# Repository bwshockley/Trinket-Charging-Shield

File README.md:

# Trinket-Battery-Shield
Adafruit Trinket Shield for Battery Charging and RGB status LED.

Version B

## About
This is an add-on circuit board for the [Adafruit Trinkets](https://www.adafruit.com/?q=trinket&).  This board adds a battery connector with an MCP73831 Lithium-Ion/Lithium-Polymer battery charger set at 100mAH charging.
The charger has two indicator LEDs, one to indicate the battery is currently charging from the micro-usb port on the Trinket, and the other to indicate when the battery has fully charged.

Version B of the board has the connections reversed such that this board and the Trinket can back connected "back-to-back" so that the reset button and from LEDs (On and #1) can be accessed.  BOM is identical.

## Boards
PCBs can be ordered direct [through OSHPARK.com](https://oshpark.com/shared_projects/fXX7IH66).

[Version B here.](https://oshpark.com/shared_projects/0WDgFbOp)

## WS2812B LED
There is a pad for a WS2812B RGB LED.  This LED is connected to data pin #0.  The user can leave this LED unpopulated if only battery charging capability is required.

## Battery Power
Note that the Adafruit Trinkets come with circuits for using the battery power and automatically switching between USB power and battery power as needed.  If the user only wishes to have battery power and not the charging capability, the user only needs to populate the JST 2-Pin connector on the back of the Trinket.

## BOM
C1, C2 = 0805 series SMT capcitors 10uF and at least 10V to be safe.
R1, R2 = 0805 resistors.  These resistors determine the current each status LED uses.  Charging LED should not sink more than 25mA, and Done LED should not source more than 35mA.
R3 = 0805 resistor at 10KOhm.  This sets the charger at 100mAh.  Other values possible.  Recommend 100mAh.

IC1 = MCP73831T battery charging IC.

J1 = JST-2_SMD - Available via Adafruit, Sparkfun, or Mouser.

LEDs = 0805 LEDs. Not necessary for circuit to work.  Recommended LEDS:

* SML-LX0805SOC-TR (Orange) Charging LED with R1 = 390Ohm minimum
* SML-LX0805SUGC-TR (Green) Charged or Done LED with R2 = 270Ohm minimum

WS2812B LED - Not necessary, but if the user chooses to add, LED must be 5050 size.

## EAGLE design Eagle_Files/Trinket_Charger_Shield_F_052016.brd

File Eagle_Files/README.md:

#Eagle Files
All files were designed with CadSoft Eagle PCB Design v7.5 (Eagle).  These files are provided AS IS and are not to be used for commercial purpose.
CadSoft provides several licensing options for Eagle, including a [Freeware license](http://www.cadsoftusa.com/download-eagle/freeware/) and a
[commercial light](http://www.cadsoftusa.com/eagle-pricing/) license.  Additional information
can be found on the [CadSoft website](http://www.cadsoftusa.com)

#BRD and SCH
The BRD (Board) files are the physical board layout files and the SCH (Schematic) files are the schematic for the circuit.

#GERBERS
I will upload the latest GERBER files as soon as possible.  GERBER files are industry standard and can be sent to almost any PCB manufacturer.
They do not require the use of CadSoft Eagle to view and use.

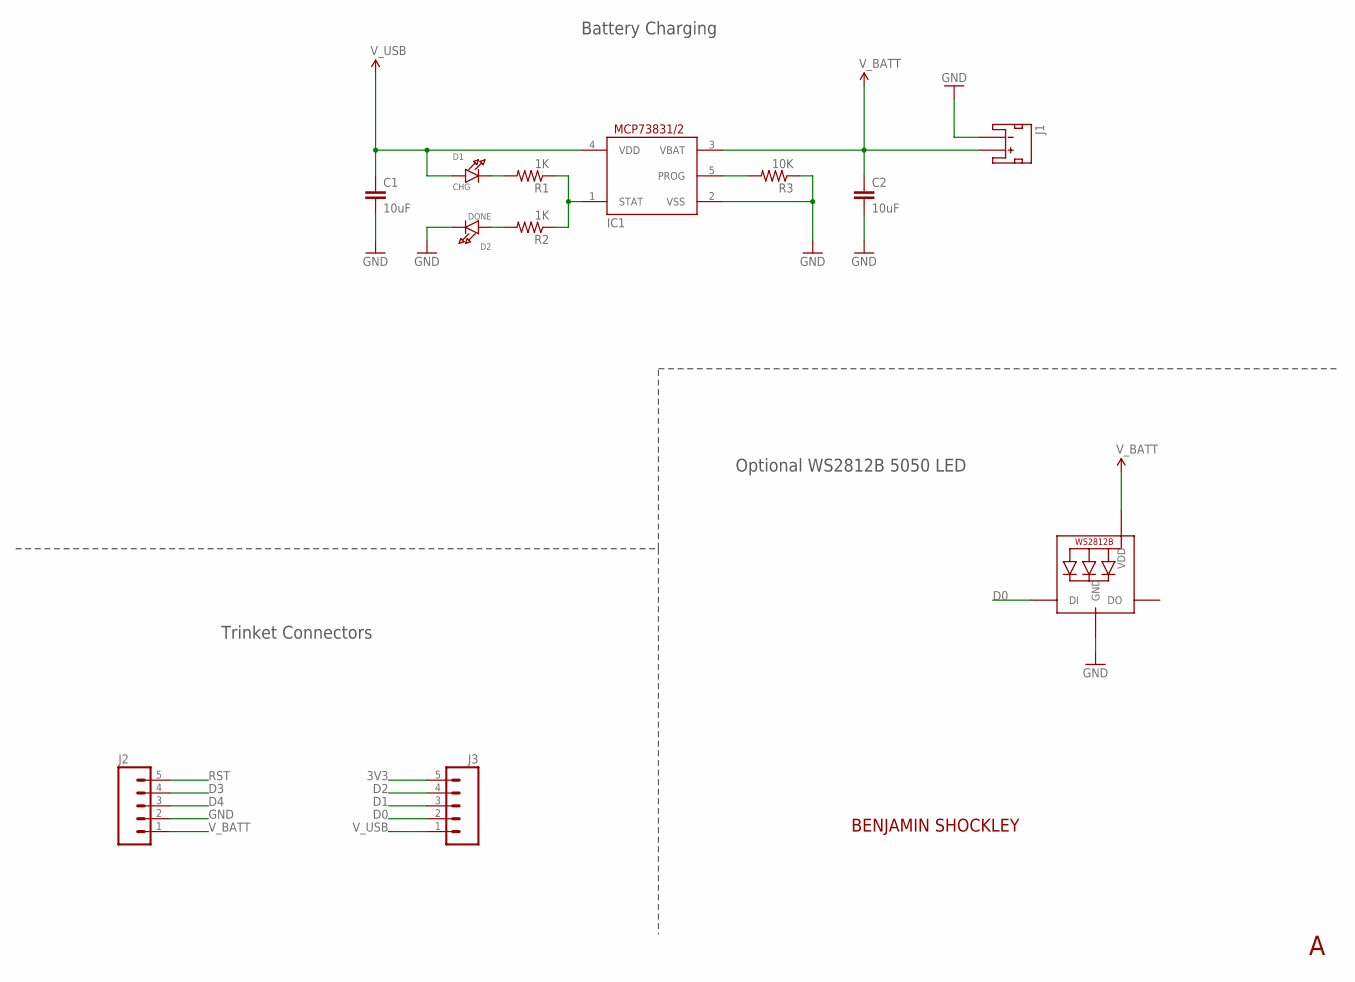
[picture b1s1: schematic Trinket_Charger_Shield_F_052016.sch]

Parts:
C1, C2: 10uF; 0805
D1: CHG; CHIPLED_0805_NOOUTLINE
D2: DONE; CHIPLED_0805_NOOUTLINE
IC1: MCP73831/OT; SOT23-5L
J1: JST_2MM_MALE; JST-2-SMD
J2, J3: M05NO_SILK; 1X05_NO_SILK
LED: WS2812B5050; WS2812B
R1, R2: 1K; 0805
R3: 10K; 0805

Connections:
3V3: J3.5
D0: J3.2, LED.4-DIN (DI)
D1: J3.3
D2: J3.4
D3: J2.4
D4: J2.3
GND: C1.2, C2.2, D2.C, IC1.2 (VSS), J1.1 (-), J2.2, LED.3-GND (GND), R3.1
unnamed: IC1.5 (PROG), R3.2
unnamed: IC1.1 (STAT), R1.1, R2.1
unnamed: D1.C, R1.2
unnamed: D2.A, R2.2
RST: J2.5
V_BATT: C2.1, IC1.3 (VBAT), J1.2 (+), J2.1, LED.1-VDD (VDD)
V_USB: C1.1, D1.A, IC1.4 (VDD), J3.1

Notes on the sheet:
Trinket Connectors
Optional WS2812B 5050 LED
Battery Charging

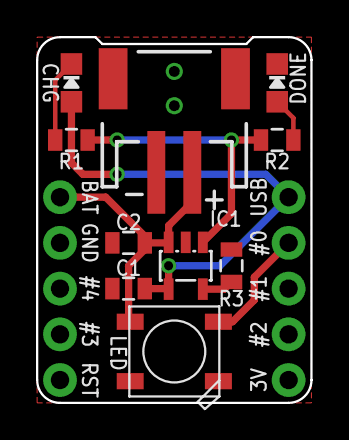
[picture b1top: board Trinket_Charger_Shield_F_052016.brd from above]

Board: 2 copper layers, 15.2 x 20.3 mm, 13 parts (1 on the bottom side), 8 nets.

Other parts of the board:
U$1: OSHW-LOGO-M

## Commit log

2016-04-26 Initial Commit
    Initial commit for the Trinket Battery Charger Shield.
2016-04-26 Create README.md
    Created the REDME file with background information and BOM for the circuit.
2016-04-26 Updated Schematic
    Updated schematic to include additional details and clean up design to
    clarify various parts of the circuit.
2016-04-26 Reroute LED VDD
    Rerouted the VDD to the WS2812B LED - Better grounding of the
    capacitors.
2016-04-26 Create .gitignore
    Created .gitignore to ignore the temporary files.
2016-04-26 Update .gitignore
    A much better .gitignore set for Eagle.
2016-04-26 Update USB Power to CHG LED
    Slight change in route of USB power to CHG LED.
2016-04-26 Removed Files
2016-04-28 Added Images of Boards
    Added images of front and back of circuit board.
2016-04-28 Update README.md with Images
    Added images of the front and back of the circuit board to the README file.
2016-04-28 Updated Board Silk
    Added the OSHW Icon and some polarity indicators for the battery connector.
2016-04-29 Updated Images
2016-04-29 New Image Files
    Update did not take. New Image Files uploaded.
2016-05-04 Updated README.md
    Fixed typos and clarification.
2016-05-04 Added Trinket Link
    Added link to Adafruit trinkets for ease.
2016-05-09 Added PCB Link
    Added link to order PCBs on OSHPark.com
2016-05-10 Create Trinket_Charger_Shield_B
    This version is designed to connect to the trinket on the back side, so the two boards connect "back-to-back". this allows for continued use of the Trinket reset button and two front LEDs (on and #1).
2016-05-10 Added Version B
    Updated to add information about Version B of the board.
2016-05-20 Uploaded latest files
    Uploaded the latest files with dates amended to file names for clarity. The shield files with the F indicate the board for the Front of the Trinket, while the files with the B indicate the board for 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

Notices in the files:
parts and their libraries:
SparkFun-Connectors: Licensing: Creative Commons ShareAlike 4.0 International - https://creativecommons.org/licenses/by-sa/4.0
microbuilder: This work is placed in the public domain, and may be freely used for commercial and non-commercial work with the following conditions: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
